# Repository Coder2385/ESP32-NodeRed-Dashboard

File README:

# ESP32-NodeRed-Dashboard

> NOTE: THIS IS AN EXPANSION OF ESP32-Sensor-Dashboard
> Import `flows.json` via **☰ → Import → select file**

It reads temperature and humidity using a BME280 sensor and streams live data to a web page using WebSockets no page refresh needed. 
The data updates instantly in the browser the moment the ESP32 has a new reading. 
This project also serves as the foundation for MQTT publishing and Node-RED dashboard visualization. 
Everything runs on millis, no delay used anywhere.

|  | 

---

## ✨ Features

- 🌡️ Measures temperature and humidity using a BME280 sensor
- 🖥️ Displays live data on an SSD1306 OLED screen (128x64)
- 📶 Creates its own WiFi hotspot
- 🌐 Local web server at `Your IP-address`
- ⚡ Live data streaming via WebSockets — no page refresh
- 📡 Foundation for MQTT publishing and Node-RED dashboard
- 📈 Statistics — min/max temperature and threshold count, updated live 
- ⚠️ Error handling for sensor failures or loose connections
- 🔒 No sensitive data in main code
- 🧠 Non-blocking timing with `millis()` → web server stays responsive
- 🖱️ Interactive button:
  - **Short press**: shows "Button pressed!" on the OLED
  - **Long press (≥ 2 sec)**: cycles through three modes:
    - 📊 Sensor Mode — live temperature and humidity
    - ℹ️ Info Mode — device IP address and uptime
    - 📈 Stats Mode — min/max temperature and threshold count
  - **Auto-return (after 5 sec)**: returns to Sensor Mode automatically
- 🌡️ Smart alert system: reacts to high temperature with LED, OLED, and web feedback

---

## ⚡ WebSockets vs Auto-refresh

Previous projects used `setTimeout` to reload the page every 2 seconds. This project uses WebSockets — a permanent connection between the browser and the ESP32. The ESP32 pushes new data directly to the browser the moment it has a new reading. No reload, no flicker, no unnecessary requests.

---

> ⚠️ **Why no `°` symbol on the OLED?**
> The `Adafruit_SSD1306` library has limited support for special characters like the degree symbol (`°`). To keep the code simple and reliable, the OLED displays only `"C"` instead of `"°C"`.
>
> ✅ The **web version** does show the correct `°C` symbol thanks to HTML encoding.

This is a common limitation in embedded displays — not a bug!

---

## 🧰 Components Required

- ESP32 Development Board (e.g., ESP32 DevKit)
- BME280 temperature/humidity sensor (I²C)
- SSD1306 OLED display (128x64, I²C)
- Breadboard and jumper wires
- Micro-USB cable
- RED LED
- 2x 220 Ohm Resistor
- 1x pushbutton

---

## 🔌 Wiring (I²C Bus)

| ESP32 Pin | Function | Connected To |
|----------|----------|--------------|
| 3.3V | Power | VCC of BME280 + OLED |
| GND | Ground | GND of BME280 + OLED + Button (one side) |
| GPIO21 | SDA | SDA of BME280 + OLED |
| GPIO22 | SCL | SCL of BME280 + OLED |
| GPIO4 | Input | Button (other side) |
| GPIO2 | Output | LED + 220Ω resistor |

Note: The button is connected between GPIO 4 and GND. The code enables the internal pull-up resistor, so no external resistor is required.

> 💡 Ensure both devices use **different I²C addresses** (BME280: `0x76`, OLED: `0x3C`).

---

## ▶️ Usage

1. Install required libraries via PlatformIO — add these to `platformio.ini`:

```ini
lib_deps =
    adafruit/Adafruit BME280 Library@^2.2.3
    adafruit/Adafruit SSD1306@^2.5.7
    adafruit/Adafruit GFX Library@^1.11.6
    mathieucarbou/ESPAsyncWebServer@^3.3.23
    mathieucarbou/AsyncTCP@^3.3.2
```

2. Upload the code to your ESP32
3. Connect to the WiFi hotspot created by the ESP32
4. Open your browser and go to `Your IP-address`
5. Watch the data update live — no refresh needed

---

## 🧠 How It Works

## Hardware (KiCad)

The hardware design for this project was created in KiCad. It contains the 
complete schematic and PCB layout for an ESP32-based sensor node.

### Components

- **ESP32 DOIT DevKit V1** (30-pin) — microcontroller
- **BME280** — temperature, humidity, and pressure sensor (I²C)
- **SSD1306 OLED** (0.96", I²C) — display
- **Push button** — user input
- **Red LED** with 220Ω current-limiting resistor — status indicator
- **10kΩ resistor** — pull-up for the button

### Design

- Schematic drawn and verified with ERC (no errors)
- BME280 and OLED share the I²C bus (SDA/SCL)
- PCB fully routed with a GND plane
- Passed the Design Rules Check (DRC) with no errors or warnings

### Files

- `*.kicad_sch` — schematic
- `*.kicad_pcb` — PCB layout
- `*.kicad_pro` — project file

### Libraries used

The ESP32 and OLED are not included in KiCad by default and come from 
community libraries:

- [ESP32 DevKit V1 (30-pin)](https://github.com/syauqibilfaqih/ESP32-DevKit-V1-DOIT)
- [SSD1306 OLED](https://github.com/V01Ddev/kicad-ssd1306-oled-library)

The ESP32 reads temperature and humidity every 2 seconds. Instead of rebuilding and sending the entire HTML page on each update, it sends only the new values via a WebSocket connection. The browser receives the values instantly and updates only the relevant parts of the page.

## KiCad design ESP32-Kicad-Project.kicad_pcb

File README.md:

# ESP32-NodeRed-Dashboard
ESP32 project that streams live temperature and humidity data to a web page using WebSockets. The browser updates instantly without any page refresh. Serves as the foundation for MQTT publishing and Node-RED dashboard visualization. No delay used anywhere, everything runs on millis. Also I have added my Kicad project for this with a schematic drawing, a PCB-editor and a 3D vieuwer to visualize how the PCB would look like.

https://github.com/user-attachments/assets/4c9549db-39d6-406f-8492-63ce14ac5b4d

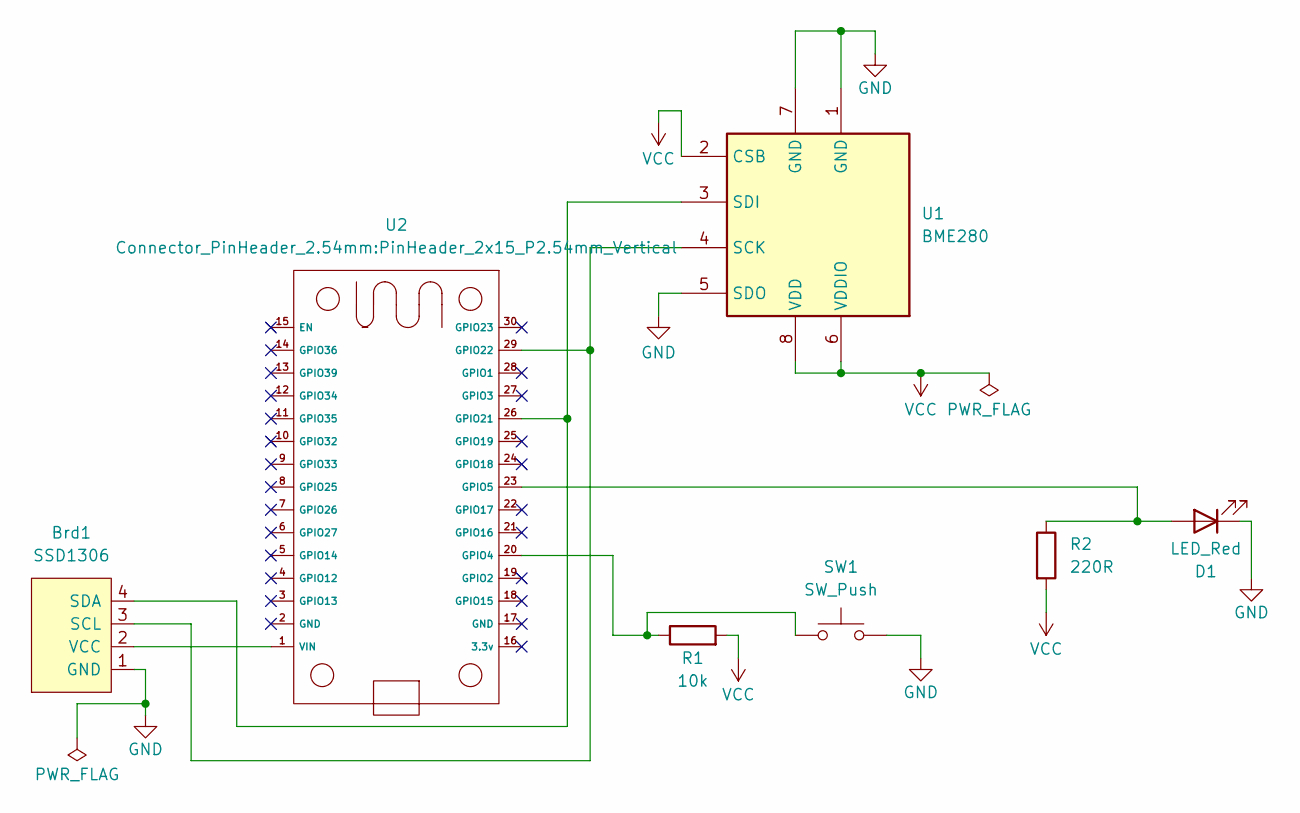
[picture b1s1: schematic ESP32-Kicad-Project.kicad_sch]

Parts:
Brd1: SSD1306; PinHeader_1x04_P2.54mm_Vertical
D1: LED_Red; LED_D5.0mm
R1: 10k; R_Axial_DIN0207_L6.3mm_D2.5mm_P10.16mm_Horizontal
R2: 220R; R_Axial_DIN0207_L6.3mm_D2.5mm_P10.16mm_Horizontal
SW1: SW_Push; SW_PUSH_6mm
U1: BME280; Bosch_LGA-8_2.5x2.5mm_P0.65mm_ClockwisePinNumbering
U2: PinHeader_2x15_P2.54mm_Vertical

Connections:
GND: Brd1.1 (GND), D1.1 (K), SW1.2, U1.1 (GND), U1.5 (SDO), U1.7 (GND)
unnamed: Brd1.3 (SCL), U1.4 (SCK), U2.29 (GPIO22)
unnamed: Brd1.4 (SDA), U1.3 (SDI), U2.26 (GPIO21)
unnamed: Brd1.2 (VCC), U2.1 (VIN)
unnamed: D1.2 (A), R2.1, U2.23 (GPIO5)
unnamed: R1.1, SW1.1, U2.20 (GPIO4)
VCC: R1.2, R2.2, U1.2 (CSB), U1.6 (VDDIO), U1.8 (VDD)

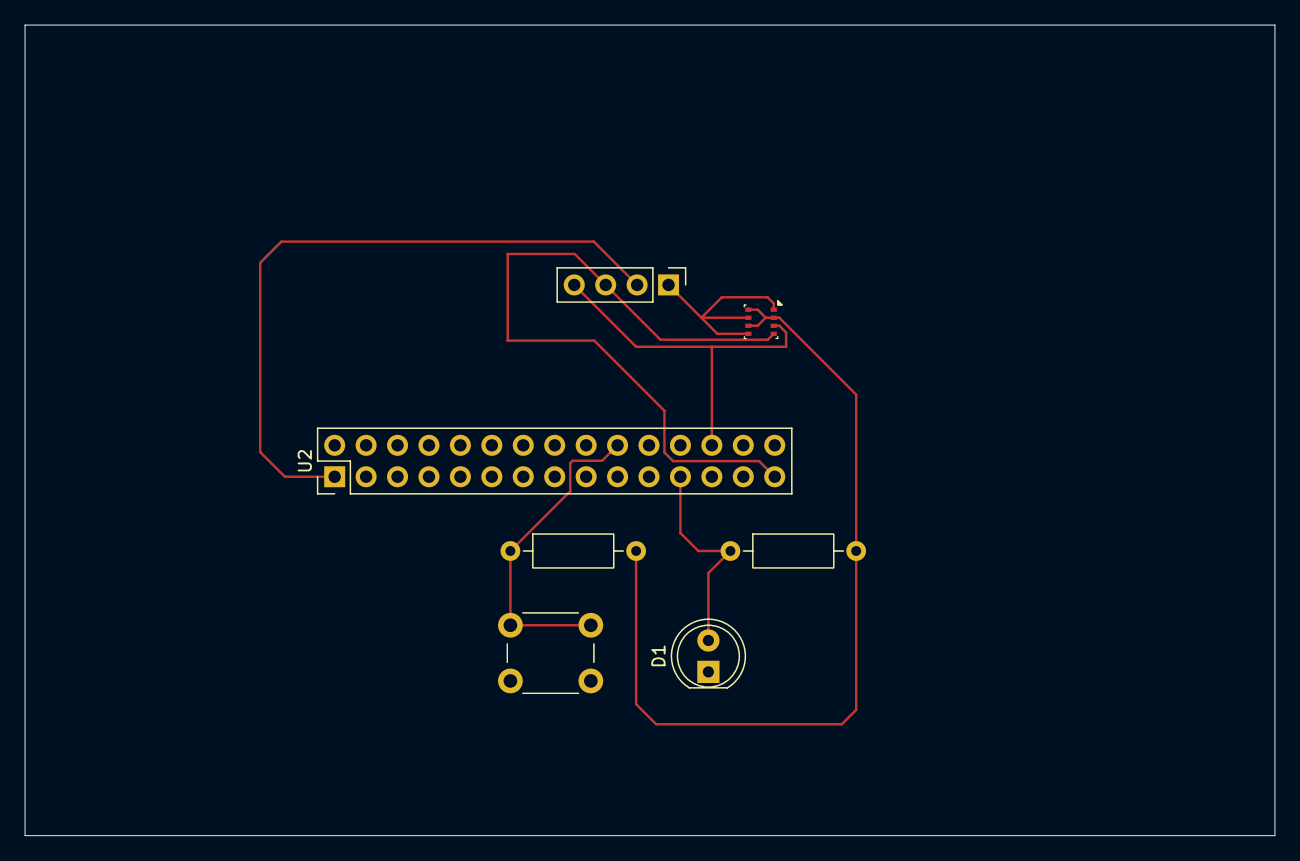
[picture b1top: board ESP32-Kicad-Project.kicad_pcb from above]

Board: 2 copper layers, 101.0 x 65.5 mm, 7 parts (0 on the bottom side), 7 nets.

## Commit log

2026-06-09 Add files via upload
    Kicad project added
